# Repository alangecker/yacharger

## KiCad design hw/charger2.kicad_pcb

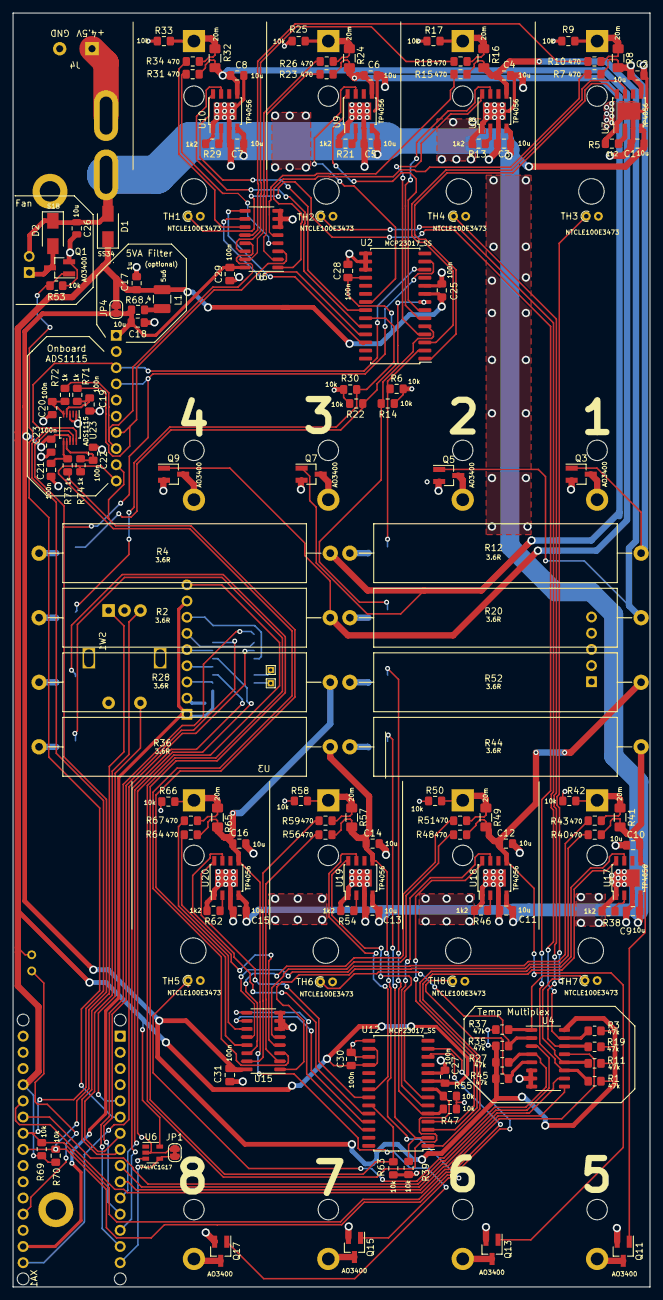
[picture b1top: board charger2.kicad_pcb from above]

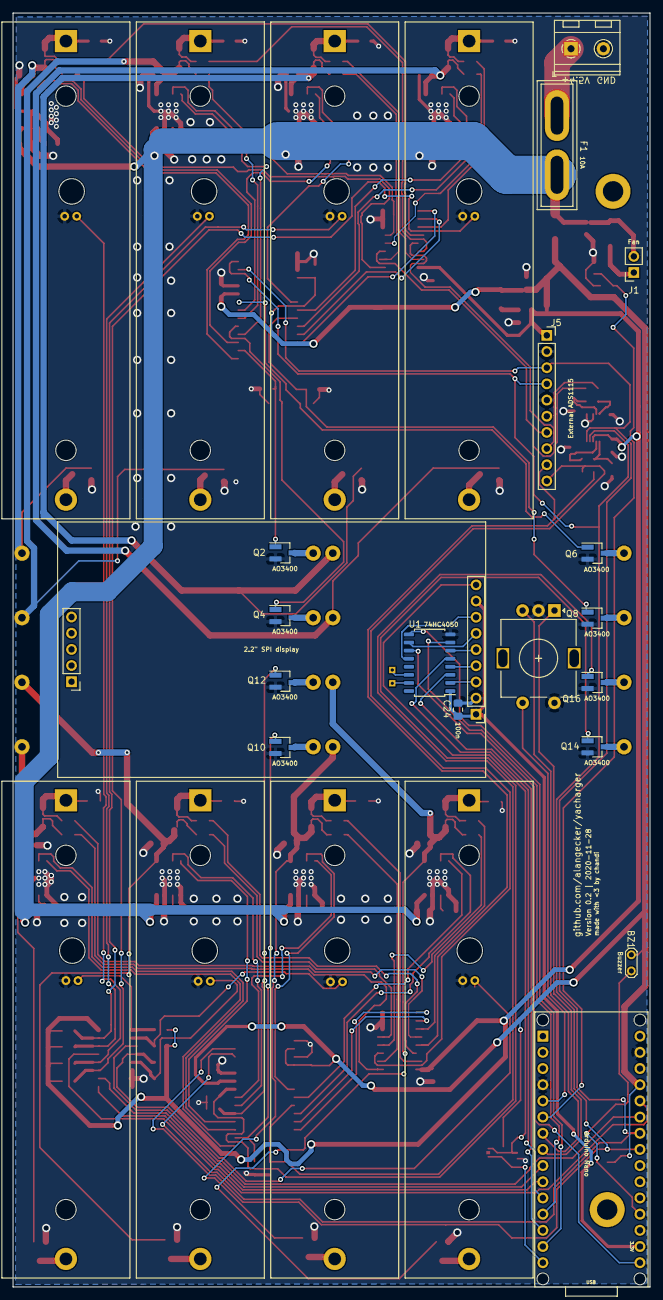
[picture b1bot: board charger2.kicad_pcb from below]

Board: 2 copper layers, 100.0 x 200.0 mm, 169 parts (26 on the bottom side), 133 nets.

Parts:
BT1, BT2, BT3, BT4, BT5, BT6, BT7, BT8: Battery_Cell; BatteryHolder_MPD_BH-18650-PC2
BZ1: Buzzer; TestPoint_2Pads_Pitch2.54mm_Drill0.8mm
C1, C2, C3, C4, C5, C6, C7, C8, C9, C10, C11, C12, C13, C14, C15, C16, C18: 10u; C_0805_2012Metric_Pad1.15x1.40mm_HandSolder
C17: 1u; C_0805_2012Metric_Pad1.15x1.40mm_HandSolder
C19, C20, C21, C22, C23, C24, C25, C27: 100n; C_0805_2012Metric_Pad1.15x1.40mm_HandSolder
C26: 10u; C_0805_2012Metric
C28, C29, C30, C31: 100n; C_0805_2012Metric_Pad1.18x1.45mm_HandSolder
D1: SS34; D_SMA
D2: S1B; D_SMA
F1: 10A; Fuse_Blade_ATO_directSolder
H1, H2: MountingHole; MountingHole_3.2mm_M3_ISO14580_Pad
J1: Fan; PinSocket_1x02_P2.54mm_Vertical
J4: 4.5V Power Supply; TerminalBlock_RND_205-00232_1x02_P5.08mm_Horizontal
J5: External ADS1115; PinSocket_1x10_P2.54mm_Vertical
JP1: MISO_JMP; SolderJumper-2_P1.3mm_Bridged_RoundedPad1.0x1.5mm
JP4: 5VA Bridge; SolderJumper-2_P1.3mm_Bridged_RoundedPad1.0x1.5mm
L1: 5u6; L_1210_3225Metric_Pad1.42x2.65mm_HandSolder
Q1, Q2, Q3, Q4, Q5, Q6, Q7, Q8, Q9, Q10, Q11, Q12, Q13, Q14, Q15, Q16, Q17: AO3400; SOT-23_Handsoldering
R1, R3, R11, R19, R27, R35, R37, R45: 47k; R_0805_2012Metric_Pad1.20x1.40mm_HandSolder
R2, R4, R12, R20, R28, R36, R44, R52: 3.6R; R_Axial_Power_L38.0mm_W9.0mm_P45.72mm
R5, R13, R21, R29, R38, R46, R54, R62: 1k2; R_0805_2012Metric_Pad1.15x1.40mm_HandSolder
R6, R9, R14, R17, R22, R25, R30, R33, R39, R42, R47, R50, R55, R58, R63, R66, R69, R70: 10k; R_0805_2012Metric_Pad1.15x1.40mm_HandSolder
R7, R10, R15, R18, R23, R26, R31, R34, R40, R43, R48, R51, R56, R59, R64, R67: 470; R_0805_2012Metric_Pad1.15x1.40mm_HandSolder
R8, R16, R24, R32, R41, R49, R57, R65: 20m; R_1206_3216Metric_Pad1.42x1.75mm_HandSolder
R53: 10k; R_0805_2012Metric_Pad1.20x1.40mm_HandSolder
R68: 4; R_0805_2012Metric_Pad1.15x1.40mm_HandSolder
R71, R72, R73, R74: 1k; R_0805_2012Metric_Pad1.15x1.40mm_HandSolder
SW1: Button; RotaryEncoder_Alps_EC11E-Switch_Vertical_H20mm
TH1, TH2, TH3, TH4, TH5, TH6, TH7, TH8: NTCLE100E3473; R_Axial_DIN0204_L3.6mm_D1.6mm_P1.90mm_Vertical
TP1, TP2: TestPoint; TestPoint_THTPad_1.0x1.0mm_Drill0.5mm
U1: 74HC4050; SOP-16_4.55x10.3mm_P1.27mm
U2, U12: MCP23017_SS; SOIC-28W_7.5x17.9mm_P1.27mm
U3: 2.2" SPI display; MSP2202_2.2inch_SPI
U4, U5, U15: 74HC4052; SO-16_3.9x9.9mm_P1.27mm
U6: 74LVC1G17; SOT-23-5
U7, U8, U9, U10, U17, U18, U19, U20: TP4056; TP4056_SOP-8-PP
U23: ADS1115; TSSOP-10_3x3mm_P0.5mm
XA1: Arduino Nano; Arduino_Nano_Socket

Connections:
+3V3: C24.1, U1.1, U3.1, U3.8, XA1.3V3
+5V: BZ1.1, C17.1, C25.1, C27.1, C28.1, C30.1, D1.1, JP4.1, L1.2, R69.2, R70.2, U2.9, U2.18, U6.5, U12.9, U12.16, U12.18, XA1.5V
+5VA: C18.1, C23.1, C29.1, C31.1, J5.1, JP4.2, R1.1, R3.1, R11.1, R19.1, R27.1, R35.1, R37.1, R45.1, R68.1, U4.16, U5.16, U15.16, U23.8
/CS: U1.3, XA1.D10
/DC: U1.7, XA1.D9
/Display/3.3_CS: U1.2, U3.3
/Display/3.3_MOSI: U1.10, U3.6
/Display/3.3_RESET: U1.4, U3.4
/Display/3.3_RS: U1.6, U3.5
/Display/3.3_SCK: U1.12, U3.7
/Display/MISO: JP1.1, U6.4, XA1.D12
/Display/MOSI: U1.9, XA1.D11
/Display/SCK: U1.11, XA1.D13
/FAN_Control/FAN_PWM: Q1.1, R53.1, XA1.D3
/MCU/A6: U4.3, XA1.A6
/MCU/A7: U4.13, XA1.A7
/MCU/BUTTON: SW1.S1, XA1.D2
/MCU/BUZZER: BZ1.2, XA1.A0
/MCU/ROT_A: SW1.A, XA1.D5
/MCU/ROT_B: SW1.B, XA1.D4
/MCU/SDA: J5.4, R70.1, U2.13, U12.13, U23.9, XA1.A4
/RST: U1.5, XA1.D8
/TempMultiplex/S_A: U4.10, XA1.D6
/TempMultiplex/S_B: U4.9, XA1.D7
/TempMultiplex/T1: R11.2, TH3.1, U4.12
/TempMultiplex/T2: R19.2, TH4.1, U4.14
/TempMultiplex/T3: R3.2, TH2.1, U4.15
/TempMultiplex/T4: R1.2, TH1.1, U4.11
/adc/AIN0: J5.7, R71.2, U5.3
/adc/AIN1: J5.8, R72.2, U5.13
/adc/AIN2: J5.9, R73.2, U15.13
/adc/AIN3: J5.10, R74.2, U15.3
/quadcharger1/Battery/Bat+: BT1.1, R8.1, R9.1, R10.2
/quadcharger1/Battery/Bat+': C2.1, Q3.1, R7.1, R8.2, R12.1, U7.5
/quadcharger1/Battery/Bat-: BT1.2, Q3.3
/quadcharger1/Battery/CE: U2.1, U7.8
/quadcharger1/Battery/CHRG: U2.3, U7.7
/quadcharger1/Battery/DE: Q2.1, R6.1, U2.2
/quadcharger1/SCK: J5.3, R69.1, U2.12, U12.12, U23.10, XA1.A5
/quadcharger1/X0: R10.1, U5.12
/quadcharger1/X1: R18.1, U5.14
/quadcharger1/X2: R26.1, U5.15
/quadcharger1/X3: R34.1, U5.11
/quadcharger1/Y0: R7.2, U5.1
/quadcharger1/Y1: R15.2, U5.5
/quadcharger1/Y2: R23.2, U5.2
/quadcharger1/Y3: R31.2, U5.4
/quadcharger1/sheet5DC5D9EA/Bat+: BT3.1, R24.1, R25.1, R26.2
/quadcharger1/sheet5DC5D9EA/Bat+': C6.1, Q7.1, R4.1, R23.1, R24.2, U9.5
/quadcharger1/sheet5DC5D9EA/Bat-: BT3.2, Q7.3
/quadcharger1/sheet5DC5D9EA/CE: U2.7, U9.8
/quadcharger1/sheet5DC5D9EA/CHRG: U2.21, U9.7
/quadcharger1/sheet5DC5D9EA/DE: Q6.1, R22.1, U2.8
/quadcharger1/sheet5DC5D930/Bat+: BT2.1, R16.1, R17.1, R18.2
/quadcharger1/sheet5DC5D930/Bat+': C4.1, Q5.1, R15.1, R16.2, R20.1, U8.5
/quadcharger1/sheet5DC5D930/Bat-: BT2.2, Q5.3
/quadcharger1/sheet5DC5D930/CE: U2.4, U8.8
/quadcharger1/sheet5DC5D930/CHRG: U2.6, U8.7
/quadcharger1/sheet5DC5D930/DE: Q4.1, R14.1, U2.5
/quadcharger1/sheet5DC5DB5C/Bat+: BT4.1, R32.1, R33.1, R34.2
/quadcharger1/sheet5DC5DB5C/Bat+': C8.1, Q9.1, R2.1, R31.1, R32.2, U10.5
/quadcharger1/sheet5DC5DB5C/Bat-: BT4.2, Q9.3
/quadcharger1/sheet5DC5DB5C/CE: U2.22, U10.8
/quadcharger1/sheet5DC5DB5C/CHRG: U2.24, U10.7
/quadcharger1/sheet5DC5DB5C/DE: Q8.1, R30.1, U2.23
/quadcharger2/Battery/Bat+: BT5.1, R41.1, R42.1, R43.2
/quadcharger2/Battery/Bat+': C10.1, Q11.1, R40.1, R41.2, R44.1, U17.5
/quadcharger2/Battery/Bat-: BT5.2, Q11.3
/quadcharger2/Battery/CE: U12.1, U17.8
/quadcharger2/Battery/CHRG: U12.3, U17.7
/quadcharger2/Battery/DE: Q10.1, R39.1, U12.2
/quadcharger2/T1: R37.2, TH7.1, U4.1
/quadcharger2/T2: R45.2, TH8.1, U4.5
/quadcharger2/T3: R35.2, TH6.1, U4.2
/quadcharger2/T4: R27.2, TH5.1, U4.4
/quadcharger2/X0: R43.1, U15.12
/quadcharger2/X1: R51.1, U15.14
/quadcharger2/X2: R59.1, U15.15
/quadcharger2/X3: R67.1, U15.11
/quadcharger2/Y0: R40.2, U15.1
/quadcharger2/Y1: R48.2, U15.5
/quadcharger2/Y2: R56.2, U15.2
/quadcharger2/Y3: R64.2, U15.4
/quadcharger2/sheet5DC5D9EA/Bat+: BT7.1, R57.1, R58.1, R59.2
/quadcharger2/sheet5DC5D9EA/Bat+': C14.1, Q15.1, R36.1, R56.1, R57.2, U19.5
/quadcharger2/sheet5DC5D9EA/Bat-: BT7.2, Q15.3
/quadcharger2/sheet5DC5D9EA/CE: U12.7, U19.8
/quadcharger2/sheet5DC5D9EA/CHRG: U12.21, U19.7
/quadcharger2/sheet5DC5D9EA/DE: Q14.1, R55.1, U12.8
/quadcharger2/sheet5DC5D930/Bat+: BT6.1, R49.1, R50.1, R51.2
/quadcharger2/sheet5DC5D930/Bat+': C12.1, Q13.1, R48.1, R49.2, R52.1, U18.5
/quadcharger2/sheet5DC5D930/Bat-: BT6.2, Q13.3
/quadcharger2/sheet5DC5D930/CE: U12.4, U18.8
/quadcharger2/sheet5DC5D930/CHRG: U12.6, U18.7
/quadcharger2/sheet5DC5D930/DE: Q12.1, R47.1, U12.5
/quadcharger2/sheet5DC5DB5C/Bat+: BT8.1, R65.1, R66.1, R67.2
/quadcharger2/sheet5DC5DB5C/Bat+': C16.1, Q17.1, R28.1, R64.1, R65.2, U20.5
/quadcharger2/sheet5DC5DB5C/Bat-: BT8.2, Q17.3
/quadcharger2/sheet5DC5DB5C/CE: U12.22, U20.8
/quadcharger2/sheet5DC5DB5C/CHRG: U12.24, U20.7
/quadcharger2/sheet5DC5DB5C/DE: Q16.1, R63.1, U12.23
GND: C1.2, C2.2, C3.2, C4.2, C5.2, C6.2, C7.2, C8.2, C9.2, C10.2, C11.2, C12.2, C13.2, C14.2, C15.2, C16.2, C17.2, C18.2, C19.2, C20.2, C21.2, C22.2, C23.2, C24.2, C25.2, C26.2, C27.2, C28.2, C29.2, C30.2, C31.2, J4.2, J5.2, J5.5, Q1.2, Q2.2, Q3.2, Q4.2, Q5.2, Q6.2, Q7.2, Q8.2, Q9.2, Q10.2, Q11.2, Q12.2, Q13.2, Q14.2, Q15.2, Q16.2, Q17.2, R5.2, R6.2, R9.2, R13.2, R14.2, R17.2, R21.2, R22.2, R25.2, R29.2, R30.2, R33.2, R38.2, R39.2, R42.2, R46.2, R47.2, R50.2, R53.2, R54.2, R55.2, R58.2, R62.2, R63.2, R66.2, SW1.C, SW1.S2, TH1.2, TH2.2, TH3.2, TH4.2, TH5.2, TH6.2, TH7.2, TH8.2, U1.8, U2.10, U2.15, U2.16, U2.17, U3.2, U4.6, U4.7, U4.8, U5.6, U5.7, U5.8, U6.3, U7.1, U7.3, U7.9, U8.1, U8.3, U8.9, U9.1, U9.3, U9.9, U10.1, U10.3, U10.9, U12.10, U12.15, U12.17, U15.6, U15.7, U15.8, U17.1, U17.3, U17.9, U18.1, U18.3, U18.9, U19.1, U19.3, U19.9, U20.1, U20.3, U20.9, U23.1, U23.3, XA1.GND1, XA1.GND2
unnamed: C19.1, R71.1, U23.4
unnamed: C20.1, R72.1, U23.5
unnamed: C21.1, R73.1, U23.6
unnamed: C22.1, R74.1, U23.7
unnamed: D2.2, J1.1, Q1.3
unnamed: F1.2, J4.1
unnamed: JP1.2, U3.9, U6.2
unnamed: L1.1, R68.2
unnamed: Q2.3, R12.2
unnamed: Q4.3, R20.2
unnamed: Q6.3, R4.2
unnamed: Q8.3, R2.2
unnamed: Q10.3, R44.2
unnamed: Q12.3, R52.2
unnamed: Q14.3, R36.2
unnamed: Q16.3, R28.2
unnamed: R5.1, U7.2
unnamed: R13.1, U8.2
unnamed: R21.1, U9.2
unnamed: R29.1, U10.2
unnamed: R38.1, U17.2
unnamed: R46.1, U18.2
unnamed: R54.1, U19.2
unnamed: R62.1, U20.2
unnamed: TP1.1, U1.14
unnamed: TP2.1, U1.15
unnamed: U2.25, U5.10
unnamed: U2.26, U5.9
unnamed: U12.25, U15.10
unnamed: U12.26, U15.9
VDD: C1.1, C3.1, C5.1, C7.1, C9.1, C11.1, C13.1, C15.1, C26.1, D1.2, D2.1, F1.1, J1.2, U7.4, U8.4, U9.4, U10.4, U17.4, U18.4, U19.4, U20.4

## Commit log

2019-11-10 multiple changes
2019-11-10 fix mux enable pin, reroute some traces
2019-11-11 v0.1
2020-02-11 sw: initial commit
2020-10-24 sw:display: fault/done view, optional temp feature, small bug fixes
2020-11-28 hw: pcb redesign
2020-12-24 fix 4052 footprint
2020-12-25 additional caps, groundplane improvements, MISO 3.3->5V
2020-12-25 DRC fixes
2021-09-03 v0.2
2021-09-03 sw: multiple changes
